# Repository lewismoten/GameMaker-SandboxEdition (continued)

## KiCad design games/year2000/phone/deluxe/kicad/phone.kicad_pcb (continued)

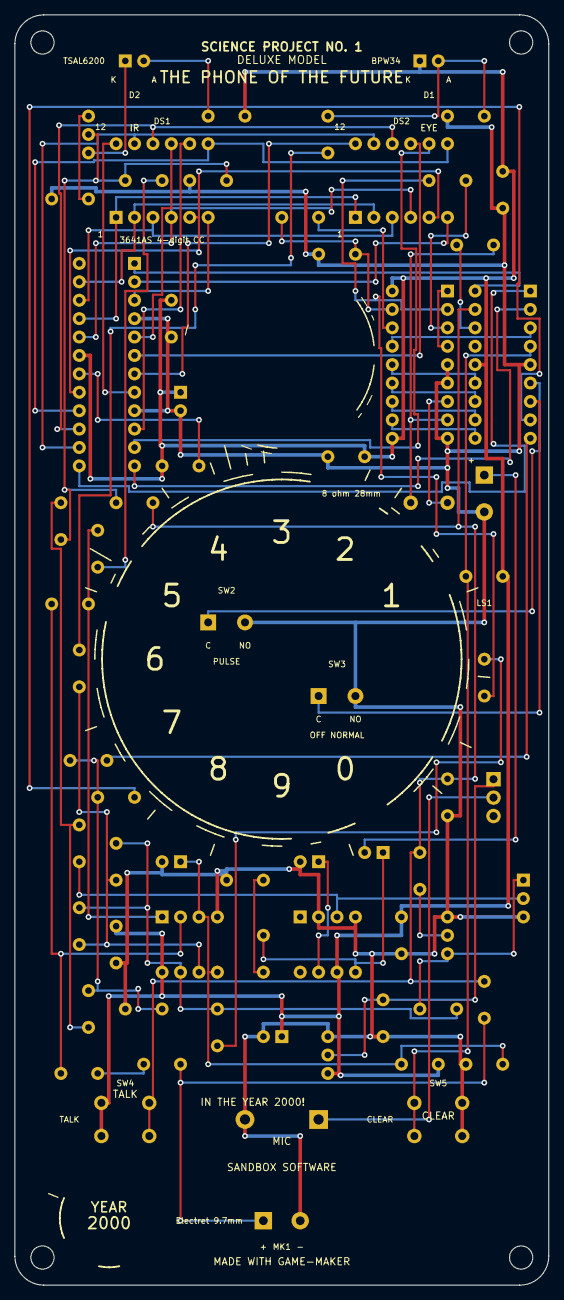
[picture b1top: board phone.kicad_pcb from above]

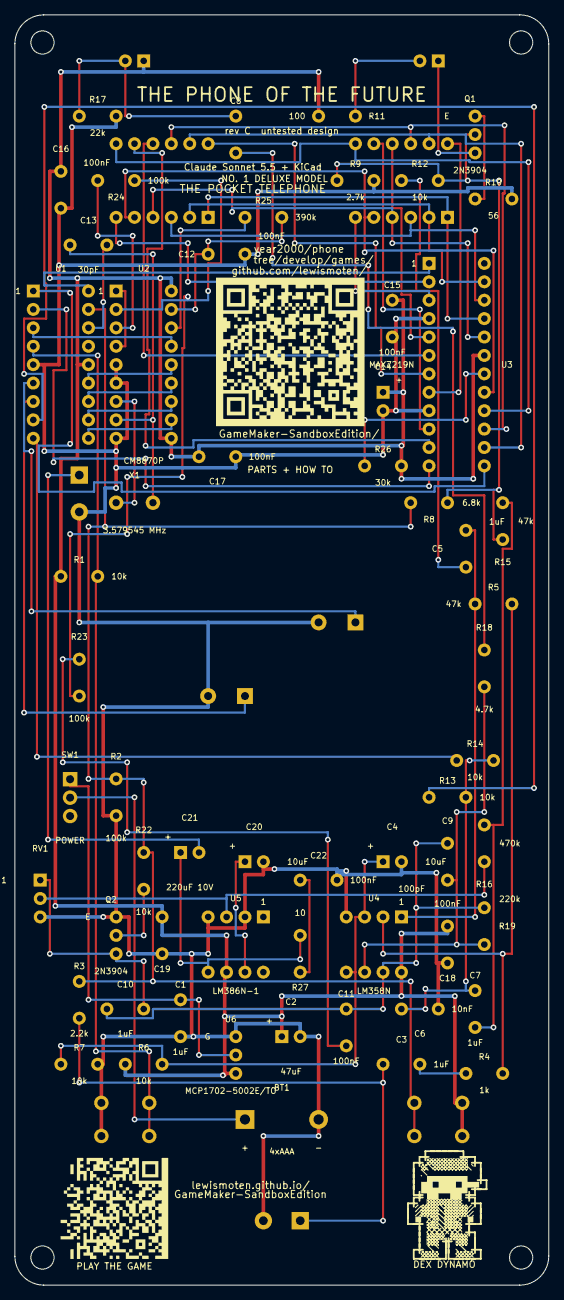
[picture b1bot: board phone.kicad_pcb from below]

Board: 2 copper layers, 73.7 x 175.3 mm, 73 parts (59 on the bottom side), 67 nets.

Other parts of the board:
H1, H2, H3, H4: M3; MountingHole_3.2mm_M3

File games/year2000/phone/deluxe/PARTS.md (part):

# Parts list: THE PHONE OF THE FUTURE (rev C)

Untested design. Part numbers are examples to start a search; check each one's drawing against the footprint before buying.
69 parts on the board, 43 different lines. Generated by `tools/bom.py` from `tools/design.py`.

| Refs | Qty | Value | Description | Side | Example part | Order at | Stock status |
|---|---|---|---|---|---|---|---|
| U1 | 1 | PIC16F628A-I/P | 8-bit microcontroller, 2K-word flash, 18-pin DIP (the one socketed part; pin-compatible with the PIC16F84A) | back | Microchip PIC16F628A-I/P (18-DIP, pin-compatible with the PIC16F84A; socketed) | Digi-Key PIC16F628A-I/P-ND $2.88 | checked 2026-11-03: Digi-Key page read, 5,817 in stock |
| U2 | 1 | CM8870P | DTMF tone decoder, 18-pin DIP; CM8870P, MT8870D and HT9170B are pin-compatible here (pins 5 and 6 tied low) | back | California Micro Devices CM8870P (or Zarlink MT8870DE, Holtek HT9170B: same 18-DIP pinout, pins 5 and 6 to ground) | Futurlec MT8870DE $1.45 / HT9170B $0.50 (no US retailer found with a plain CM8870P; Digi-Key's MT8870DE1 is obsolete) | checked 2026-11-03: pin compatibility from the CM8870 and HT9170 datasheets; Futurlec prices read, stock not shown |
| U3 | 1 | MAX7219N | 8-digit LED display driver, 24-pin 0.3in DIP (HGSEMI MAX7219N clone; Maxim MAX7219CNG+ also fits) | back | HGSEMI MAX7219N (clone, DIP-24; Maxim MAX7219CNG+ also fits) | LCSC C492111 about $1.57 (the Maxim part is $23.97 at Digi-Key MAX7219CNG+-ND) | checked 2026-11-03: LCSC page names part and package; its stock and price were not on the page I read (a search snippet showed 26 to 28 in stock, 1+ $1.57): unconfirmed |
| U4 | 1 | LM358N | Dual op-amp (mic preamp and IR receive amp), 8-pin DIP | back | TI LM358N (LM358P) | Digi-Key LM358N/NOPB | unchecked |
| U5 | 1 | LM386N-1 | Audio power amplifier, 8-pin DIP | back | TI LM386N-1 | Digi-Key LM386N-1/NOPB | unchecked |
| U6 | 1 | MCP1702-5002E/TO | 5 V low-dropout regulator, TO-92 (pin 1 gnd, 2 in, 3 out; 250 mA, 0.65 V dropout at 250 mA) | back | Microchip MCP1702-5002E/TO (TO-92, 5.0 V, 250 mA, 0.65 V dropout max at 250 mA, 13.2 V max in; pin 1 GND, 2 IN, 3 OUT) | Digi-Key MCP1702-5002E/TO-ND $0.65 | checked 2026-11-03: Digi-Key page read, 2,783 in stock; pinout and dropout from the MCP1702 datasheet DS22008E |
| Q1 | 1 | 2N3904 | NPN transistor, IR LED driver | back | onsemi 2N3904 (TO-92) | Jameco / Digi-Key 2N3904 | unchecked |
| Q2 | 1 | 2N3904 | NPN transistor, mutes the receiver while TALK is held or a digit is being sent | back | onsemi 2N3904 (TO-92) | Jameco / Digi-Key 2N3904 | unchecked |
| X1 | 1 | 3.579545 MHz | Crystal 3.579545 MHz, HC-49 (the MT8870 clock, shared with the PIC) | back | Abracon ABL-3.579545MHZ-B2 (HC-49/US) | Digi-Key 535-9099-ND (verify) | unchecked |
| D1 | 1 | BPW34 | Silicon PIN photodiode (IR receiver) | front | Vishay BPW34 (PIN photodiode) | Digi-Key / Mouser BPW34 | unchecked |
| DS1,DS2 | 2 | 3641AS 4-digit CC | 4-digit 7-segment LED module, common cathode, red, 12 pins | front | Futurlec 7FR3641AS 4-digit 0.36 in common-cathode red module (3641AS pinout) | Futurlec 7FR3641AS $1.20 (Tayda A-1775 about $0.88, stock unconfirmed) | checked 2026-11-03: pinout, 10.16 mm row spacing and 30 x 14 x 7.2 mm from the GNQ-3641 datasheet; the retailer unit was not seen |
| D2 | 1 | TSAL6200 | IR LED 940 nm, 5 mm | front | Vishay TSAL6200 (940 nm, 5 mm) | Digi-Key / Mouser TSAL6200 | unchecked |
| MK1 | 1 | Electret 9.7mm | Electret microphone capsule, solder pads | front | Electret capsule 9.7 mm, e.g. CUI CMC-9745 series | Digi-Key / Mouser CUI CMC-97 | unchecked |
| LS1 | 1 | 8 ohm 28mm | Small 8 ohm speaker, 28 mm, solder tabs | front | 8 ohm 0.25 W speaker, about 28 mm | Jameco / Digi-Key (any 28 mm 8 ohm) | unchecked |
| SW1 | 1 | POWER | Slide switch SPDT (one throw unused) | back | SPDT slide switch, 2.54 mm pins (Adafruit 805 style) | Adafruit 805 $0.95 | checked 2026-11-03: Adafruit page, in stock |
| SW2,SW3 | 2 | PULSE / OFF NORMAL | Subminiature lever microswitch (dial pulse cam); Subminiature lever microswitch (dial off-normal) | front | Omron SS-5GL2 (verify terminals) | Digi-Key / Mouser SS-5GL2 | unchecked |
| SW4,SW5 | 2 | TALK / CLEAR | 6 mm tactile switch | front | Omron B3F-1000 (6 mm tactile) | Digi-Key SW400-ND $0.35 | checked 2026-11-03: Digi-Key 21,251 in stock |
| BT1 | 1 | 4xAAA | 4 x AAA battery holder with wire leads (stuck behind the dial), leads soldered to two pads | back | Pololu 1145 4 x AAA holder with 6 in leads (53 x 50 x 13 mm) | Pololu 1145 $2.54; Digi-Key SBH441A-ND $3.48 | checked 2026-11-03: prices read, Digi-Key 88 in stock |
| R1,R6,R7,R12,R13,R14,R22 | 7 | 10k | resistors, see the schematic for each one's job | back | CFR-12JB-52-10K (Yageo 1/8 W, 5%) | Digi-Key CFR-12JB-52-10K | unchecked |
| RV1 | 1 | 10k thumbwheel | Volume: a side thumbwheel pot at the board edge, its wheel through a slot in the shell (receiver to speaker amp; the amp's own 50k input loads the wiper) | back | CFR-12JB-52-10Kthumbwheel (Yageo 1/8 W, 5%) | Digi-Key CFR-12JB-52-10Kthumbwheel | unchecked |
| R2,R23,R24 | 3 | 100k | TALK line pull-down; MT8870 input resistor; MT8870 feedback (unity gain) | back | CFR-12JB-52-100K (Yageo 1/8 W, 5%) | Digi-Key CFR-12JB-52-100K | unchecked |
| R3 | 1 | 2.2k | mic bias (powered only while TALK is held) | back | CFR-12JB-52-2.2K (Yageo 1/8 W, 5%) | Digi-Key CFR-12JB-52-2.2K | unchecked |
| R4 | 1 | 1k | mic amp input | back | CFR-12JB-52-1K (Yageo 1/8 W, 5%) | Digi-Key CFR-12JB-52-1K | unchecked |
| R5,R15 | 2 | 47k | mic amp feedback (gain 47); tones into the IR driver | back | CFR-12JB-52-47K (Yageo 1/8 W, 5%) | Digi-Key CFR-12JB-52-47K | unchecked |
| R8 | 1 | 6.8k | IR LED bias: on only while TALK is held or a digit is sent (the PIC drives TALK_H) | back | CFR-12JB-52-6.8K (Yageo 1/8 W, 5%) | Digi-Key CFR-12JB-52-6.8K | unchecked |
| R9 | 1 | 2.7k | IR LED bias | back | CFR-12JB-52-2.7K (Yageo 1/8 W, 5%) | Digi-Key CFR-12JB-52-2.7K | unchecked |
| R10 | 1 | 56 | IR LED emitter resistor | back | CFR-12JB-52-56 (Yageo 1/8 W, 5%) | Digi-Key CFR-12JB-52-56 | unchecked |
| R11 | 1 | 100 | IR LED series resistor | back | CFR-12JB-52-100 (Yageo 1/8 W, 5%) | Digi-Key CFR-12JB-52-100 | unchecked |
| R16 | 1 | 470k | tones to the speaker | back | CFR-12JB-52-470K (Yageo 1/8 W, 5%) | Digi-Key CFR-12JB-52-470K | unchecked |
| R17 | 1 | 22k | photodiode load | back | CFR-12JB-52-22K (Yageo 1/8 W, 5%) | Digi-Key CFR-12JB-52-22K | unchecked |
| R18 | 1 | 4.7k | receive amp input | back | CFR-12JB-52-4.7K (Yageo 1/8 W, 5%) | Digi-Key CFR-12JB-52-4.7K | unchecked |
| R19 | 1 | 220k | receive amp feedback (gain 47) | back | CFR-12JB-52-220K (Yageo 1/8 W, 5%) | Digi-Key CFR-12JB-52-220K | unchecked |
| R25 | 1 | 390k | MT8870 steering resistor | back | CFR-12JB-52-390K (Yageo 1/8 W, 5%) | Digi-Key CFR-12JB-52-390K | unchecked |
| R26 | 1 | 30k | MAX7219 segment current (about 7 mA) | back | CFR-12JB-52-30K (Yageo 1/8 W, 5%) | Digi-Key CFR-12JB-52-30K | unchecked |
| R27 | 1 | 10 | speaker output Zobel network | back | CFR-12JB-52-10 (Yageo 1/8 W, 5%) | Digi-Key CFR-12JB-52-10 | unchecked |
| C1,C3,C5,C7,C10 | 5 | 1uF | regulator input; mic coupling; mic amp to IR driver coupling; tone coupling; receive coupling | back | Vishay K104K15X7RF5TL2 style 5.08 mm ceramic (1uF) | Mouser 594-K104K15X7RF5TL2 (100 nF); other values similar | unchecked |
| C2 | 1 | 47uF | regulator output (1 uF minimum; electrolytic is fine) | back | Panasonic EEU-FR radial electrolytic (47uF) | Digi-Key / Mouser EEU-FR1A (10 V) | unchecked |
| C4,C14,C20 | 3 | 10uF | half-supply filter; MAX7219 supply; LM386 bypass | back | Panasonic EEU-FR radial electrolytic (10uF) | Digi-Key / Mouser EEU-FR1A (10 V) | unchecked |
| C6 | 1 | 10nF | tone low-pass | back | Vishay K104K15X7RF5TL2 style 5.08 mm ceramic (10nF) | Mouser 594-K104K15X7RF5TL2 (100 nF); other values similar | unchecked |
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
